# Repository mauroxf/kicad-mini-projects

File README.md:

## KiCad Mini Projects

**KiCad Mini Projects** is a growing collection of hardware PCB designs built entirely in KiCad. Each project is **fully completed through all stages of the PCB design cycle** — including schematic capture, PCB layout, 3D rendering, and BOM generation.

> **Please Note:** These designs are **not physically fabricated**, but they are fully compliant with JLCPCB manufacturing constraints and are ready to be manufactured.

---

### Goals

- **Build professional PCB designs in KiCad**
- **Practice embedded and analog layout skills**
- **Demonstrate ability to complete full design cycles**
- **Showcase experience for hardware/embedded engineering positions**

---

### Structure

Each project includes:
- `KiCad_files/` **Schematic (.kicad_sch)** and **Layout (.kicad_pcb)**
- `BOM/` **Bill of Materials (JLCPCB Ready) and/or Amazon Links**
- `exports/` **3D Render** and **PNG Files**
- `libraries/` **KiCad symbol/footprint libraries for any external components**
- `datasheets/` **Datasheets for key project components**
- `DESC.md` **Explaining design overview and results**

---

### Projects

| Project | Description | MCU / Chipset |
|---------|-------------|----------------|
| [USB to Serial Converter](./USB_to_Serial) | USB-C to 3.3V UART bridge with CH340C + ESP32 headers | CH340C + ESP32 |
| [ESP32 AI Camera](./ESP32_AI_CAM) | Modular ESP32-CAM board with SSD1306 OLED, servo headers, and boot support | ESP32-CAM |

*More projects coming soon*

---

### Skills Learned

- **Schematic Capture and Circuit Design**  
  Developed the ability to translate functional requirements into accurate schematics, including power regulation, signal conditioning, GPIO expansion, and sensor/peripheral interfacing.

- **PCB Layout and Routing (2-Layer Boards)**  
  Gained hands-on experience in component placement, DRC-compliant routing, via management, and trace width calculations for power and signal paths — with attention to EMI, clearance, and manufacturability.

- **Power Delivery and Grounding Strategy**  
  Implemented clean power distribution and ground practices using voltage regulators, decoupling capacitors, via stitching, and star grounding — supporting both 3.3V and 5V domains.

- **Connector and Peripheral Integration**  
  Integrated modules like ESP32, USB-C, OLED displays, servo headers, and custom footprints while accounting for mechanical constraints and pinout accuracy.

- **BOM Management and Design Documentation**  
  Created organized project folders with schematics, layout files, 3D renders, and visuals. Included part sourcing (BOM & Amazon links), custom footprints/symbols, and detailed READMEs.

- **Open Hardware & GitHub Workflow**  
  Practiced modular project documentation and GitHub repo structure with clear commits, license files, and image previews — aligned with open-source hardware sharing standards.

---

### License

All designs in this repository are released under the [MIT License](./LICENSE). You are free to use, modify, and share them.

---

> This repository is a live portfolio of my PCB Design learning progress

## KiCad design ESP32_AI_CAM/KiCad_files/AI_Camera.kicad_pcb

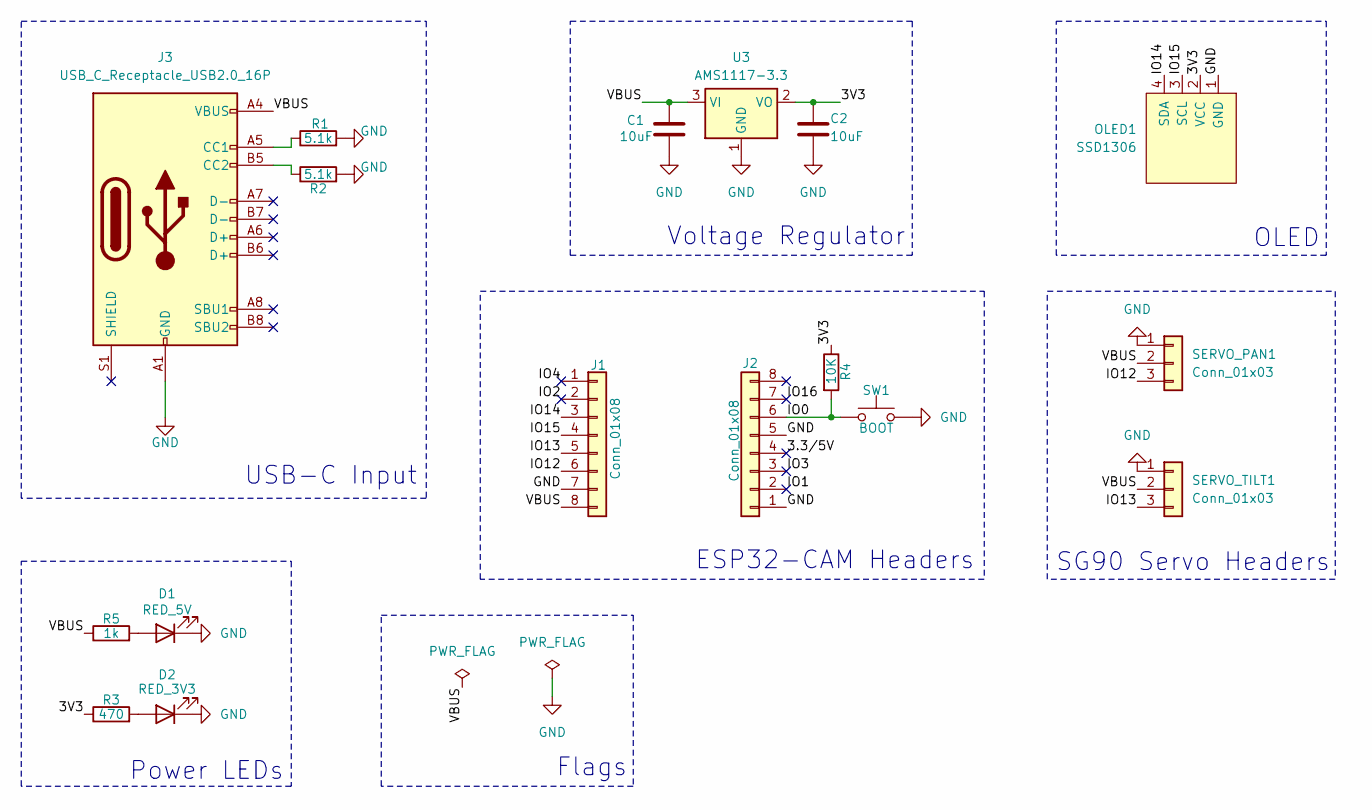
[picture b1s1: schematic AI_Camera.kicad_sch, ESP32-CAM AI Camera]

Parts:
C1, C2: 10uF; C_0603_1608Metric
D1: RED_5V; LED_0603_1608Metric
D2: RED_3V3; LED_0603_1608Metric
J1, J2: Conn_01x08; PinHeader_1x08_P2.54mm_Vertical
J3: USB_C_Receptacle_USB2.0_16P; USB_C_Receptacle_GCT_USB4105-xx-A_16P_TopMnt_Horizontal
OLED1: SSD1306; 128x64OLED
R1, R2: 5.1k; R_0603_1608Metric
R3: 470; R_0603_1608Metric
R4: 10K; R_0603_1608Metric
R5: 1k; R_0603_1608Metric
SERVO_PAN1: Conn_01x03; PinHeader_1x03_P2.54mm_Vertical
SERVO_TILT1: Conn_01x03; PinHeader_1x03_P2.54mm_Vertical
SW1: BOOT; SW_SPST_EVQP2_ShortPushTravel_H2.5mm
U3: AMS1117-3.3; SOT-223-3_TabPin2

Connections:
/3.3/5V: J2.4
/3V3: C2.1, OLED1.2 (VCC), R3.1, R4.1, U3.2 (VO)
/IO0: J2.6, R4.2, SW1.1
/IO1: J2.2
/IO2: J1.2
/IO3: J2.3
/IO4: J1.1
/IO12: J1.6, SERVO_PAN1.3
/IO13: J1.5, SERVO_TILT1.3
/IO14: J1.3, OLED1.4 (SDA)
/IO15: J1.4, OLED1.3 (SCL)
/IO16: J2.7
/VBUS: C1.1, J1.8, J3.A4 (VBUS), J3.A9 (VBUS), J3.B4 (VBUS), J3.B9 (VBUS), R5.1, SERVO_PAN1.2, SERVO_TILT1.2, U3.3 (VI)
GND: C1.2, C2.2, D1.1 (K), D2.1 (K), J1.7, J2.1, J2.5, J3.A1 (GND), J3.A12 (GND), J3.B1 (GND), J3.B12 (GND), OLED1.1 (GND), R1.2, R2.2, SERVO_PAN1.1, SERVO_TILT1.1, SW1.2, U3.1 (GND)
unnamed: D1.2 (A), R5.2
unnamed: D2.2 (A), R3.2
unnamed: J3.A5 (CC1), R1.1
unnamed: J3.B5 (CC2), R2.1

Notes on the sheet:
Voltage Regulator
Power LEDs
OLED
ESP32-CAM Headers
Flags
SG90 Servo Headers
USB-C Input

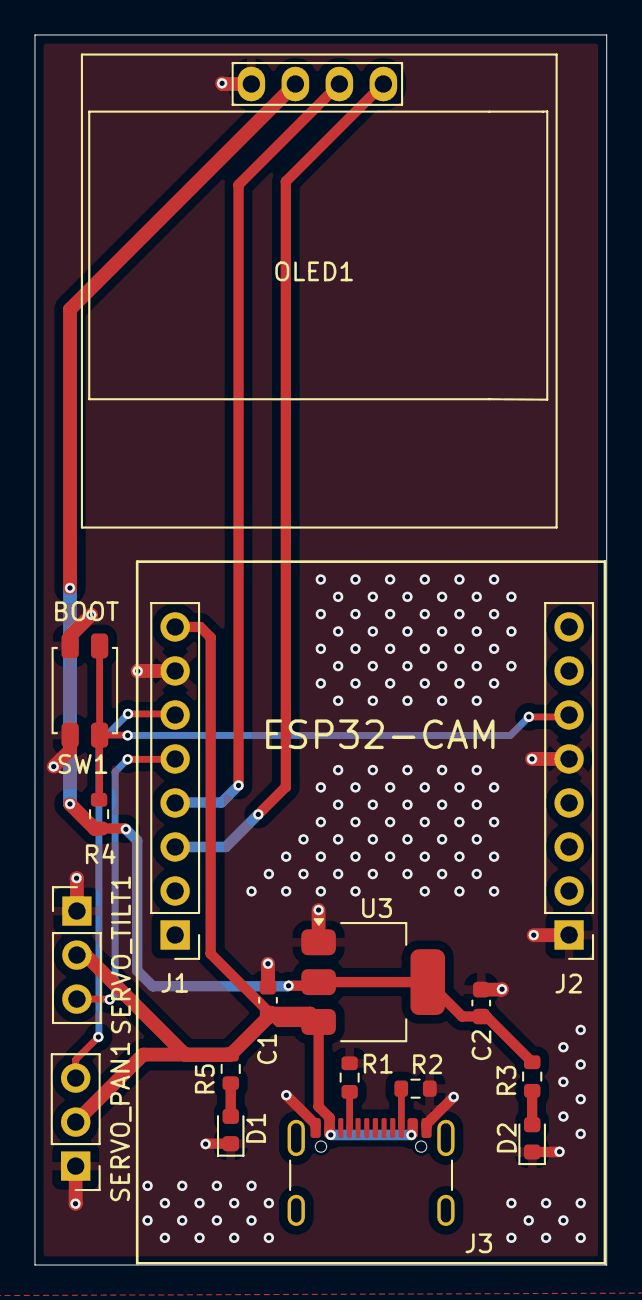
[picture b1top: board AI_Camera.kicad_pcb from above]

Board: 2 copper layers, 33.0 x 71.0 mm, 17 parts (0 on the bottom side), 12 nets.

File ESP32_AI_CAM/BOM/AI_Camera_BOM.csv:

Comment,Designator,Footprint,JLCPCB Part #
10uF,"C1, C2",Capacitor_SMD:C_0603_1608Metric ,C19702
RED LEDs,"D1, D2",LED_SMD:LED_0603_1608Metric,C2286
USB C 16 Pin Connector,J3,Connector_USB:USB_C_Receptacle_GCT_USB4105-xx-A_16P_TopMnt_Horizontal,C165948
5.1 kΩ,"R1, R2, R5",Resistor_SMD:R_0603_1608Metric,C23186
470 Ω,R3,Resistor_SMD:R_0603_1608Metric,C23162
10 kΩ,R4,Resistor_SMD:R_0603_1608Metric,C25804
Button Switch SMD H2.5mm,SW1,Button_Switch_SMD:SW_SPST_EVQP2_ShortPushTravel_H2.5mm,C273519
AMS1117-3.3,U3,Package_TO_SOT_SMD:SOT-223-3_TabPin2,C6186
"Female 1x8 Pinheader 2.54mm, THT, Hand-solder","J1, J2 ",Connector_PinHeader_2.54mm:PinHeader_1x08_P2.54mm_Vertical,DNP
"Female 1x3 Pinheader 2.54mm, THT, Hand-solder","SERVO_PAN1, SERVO_TILT1",Connector_PinHeader_2.54mm:PinHeader_1x03_P2.54mm_Vertical,DNP
"Female 1x4 pinheaded 2.54mm, THT, Hand-solder",OLED1 ,Connector_PinHeader_2.54mm:PinHeader_1x04_P2.54mm_Vertical,DNP

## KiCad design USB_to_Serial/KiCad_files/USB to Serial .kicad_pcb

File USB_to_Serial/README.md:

## USB to Serial Converter (CH340C + ESP32)

A compact USB-to-Serial interface board built around the CH340C and ESP32-WROOM-32E, designed in KiCad. Useful for debugging, flashing firmware, or serial interfacing.

### Features
- USB-C input
- AMS1117-based 3.3V regulation
- CH340C for USB-to-UART conversion
- ESP32-WROOM-32E footprint
- Status LED
- Clean routing and optimized trace widths

### Schematic & Layout

*Schematic:*

*PCB Layout:*

*Render:*

### Skills Demonstrated
- PCB layout in KiCad (2-layer)
- Component footprint and symbol management
- USB routing (D+/D- impedance aware)
- Power distribution (VBUS to LDO to 3.3V)
- Schematic capture and electrical rule checking

### Files
- `KiCad_files/` contains editable schematic and pcb layout files
- `exports/` contains rendered schematic and board images
- `BOM/` includes component list for sourcing

### License
[MIT License](LICENSE)

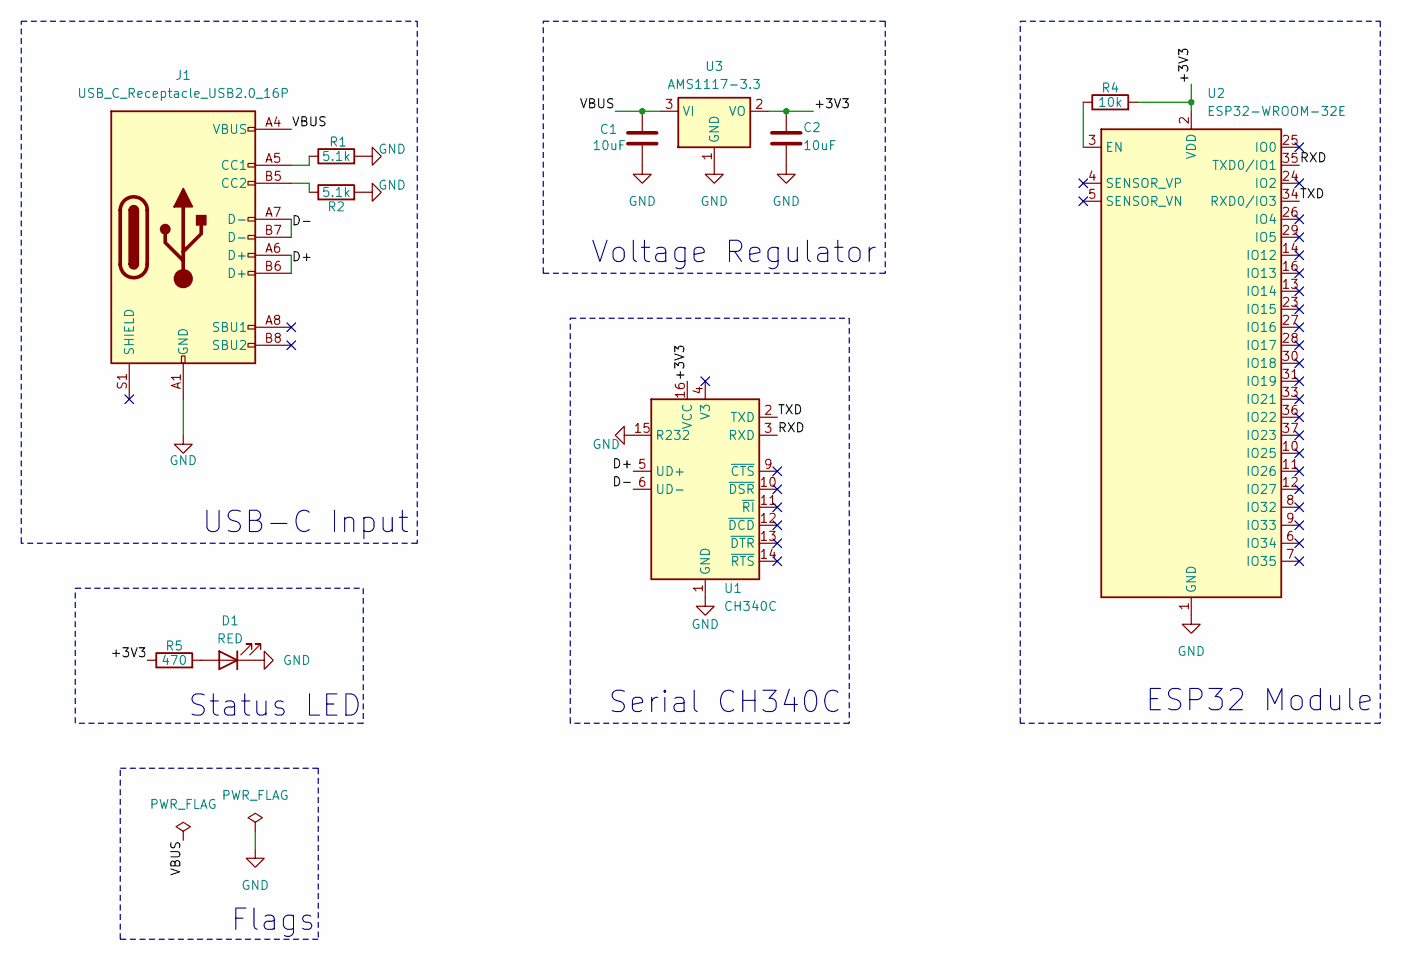
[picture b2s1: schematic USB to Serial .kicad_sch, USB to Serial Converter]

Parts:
C1, C2: 10uF; C_0603_1608Metric
D1: RED; LED_0603_1608Metric
J1: USB_C_Receptacle_USB2.0_16P; USB_C_Receptacle_GCT_USB4105-xx-A_16P_TopMnt_Horizontal
R1, R2: 5.1k; R_0603_1608Metric
R4: 10k; R_0603_1608Metric
R5: 470; R_0603_1608Metric
U1: CH340C; SOIC-16_3.9x9.9mm_P1.27mm
U2: ESP32-WROOM-32E
U3: AMS1117-3.3; SOT-223-3_TabPin2

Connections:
/+3V3: C2.1, R4.2, R5.1, U1.16 (VCC), U2.2 (VDD), U3.2 (VO)
/D+: J1.A6 (D+), J1.B6 (D+), U1.5 (UD+)
/D-: J1.A7 (D-), J1.B7 (D-), U1.6 (UD-)
/RXD: U1.3 (RXD), U2.35 (TXD0/IO1)
/TXD: U1.2 (TXD), U2.34 (RXD0/IO3)
/VBUS: C1.1, J1.A4 (VBUS), J1.A9 (VBUS), J1.B4 (VBUS), J1.B9 (VBUS), U3.3 (VI)
GND: C1.2, C2.2, D1.1 (K), J1.A1 (GND), J1.A12 (GND), J1.B1 (GND), J1.B12 (GND), R1.2, R2.2, U1.1 (GND), U1.15 (R232), U2.1 (GND), U2.15 (GND), U2.38 (GND), U2.39 (GND), U3.1 (GND)
unnamed: D1.2 (A), R5.2
unnamed: J1.A5 (CC1), R1.1
unnamed: J1.B5 (CC2), R2.1
unnamed: R4.1, U2.3 (EN)

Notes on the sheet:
Status LED
USB-C Input
Flags
ESP32 Module
Serial CH340C
Voltage Regulator

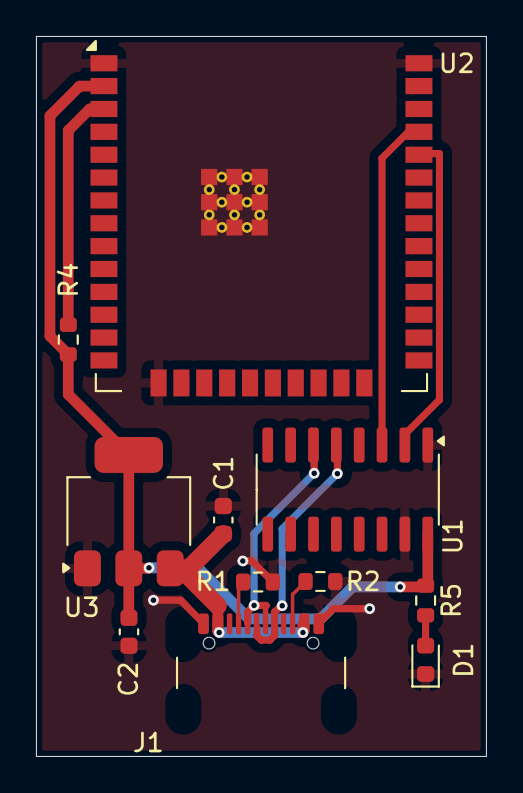
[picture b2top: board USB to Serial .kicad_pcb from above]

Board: 2 copper layers, 25.0 x 40.0 mm, 11 parts (0 on the bottom side), 11 nets.

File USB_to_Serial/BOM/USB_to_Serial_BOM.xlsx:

Comment | Designator | Footprint | JLCPCB Part #
10 uF (2 count) | C1, C2 | Capacitor_SMD:C_0603_1608Metric | C19702
5.1 kΩ (2 count) | R1, R2 | Resistor_SMD:R_0603_1608Metric | C23186
10 kΩ | R4 | Resistor_SMD:R_0603_1608Metric | C25804
470 Ω | R5 | Resistor_SMD:R_0603_1608Metric | C23162
Red LED | D1 | LED_SMD:LED_0603_1608Metric | C2286
CH340C USB–Serial IC | U1 | Package_SO:SOIC-16_3.9x9.9mm_P1.27mm | C14267
ESP32-WROOM-32E | U2 | RF_Module:ESP32-WROOM-32E | C19949066
AMS1117-3.3 Regulator | U3 | Package_TO_SOT_SMD:SOT-223-3_TabPin2 | C6186
USB-C 16 Pin Connector | J1 | Connector_USB:USB_C_Receptacle_GCT_USB4105-xx-A_16P_TopMnt_Horizontal | C165948

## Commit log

2025-07-28 Create KiCad_files
2025-07-28 Create temp
2025-07-28 Rename USB to Serial 3D-2.png to USB_to_Serial_3D-2.png
2025-07-28 Rename USB to Serial TopView.png to USB_to_Serial_Top.png
2025-07-28 Rename USB to Serial Schematic.pdf to USB_to_Serial_Schematic.pdf
2025-07-28 Rename USB to Serial 3D.png to USB_to_Serial_3D.png
2025-07-28 Rename README.md to DESC.md
2025-07-28 Create LICENSE
2025-07-28 Rename USB_to_Serial_Schematic.pdf to USB_to_Serial_Schematic.png
2025-07-30 Rename readme.md to readme.md
